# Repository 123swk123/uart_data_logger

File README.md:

# UART data logger to SD card

> [!NOTE]
> *Work in progress...*

This is a simple UART data logger, logger saves the data to FAT(12/16/32) formatted SD card.

## Schematic

## Preparations

- Any SDHC card should work, but I have tested them upto 8GB
- Format the card as FAT12/16/32
- copy the [config.txt](src/card_config/config.txt) and [head](src/card_config/head) to root of the SD card

## How to use the logger

- After power-on the status LED will be OFF
- start/stop button is a simple toggle switch
    - press once to start logging
    - press again to stop logging
- Always remove the card when status LED is OFF.

| Status LED | Remarks |
|--|--|
| OFF | Logger stopped, free to remove the SD card after powering down |
| ON | Logger running, do not remove the card |
| Constant blinking | Logger error |
| Brief pulsing |  Actively logging the received UART data |

### config.txt

first 2 lines are comment and they are skipped during the configuration process

3rd line describes the serial port configuration.
> `s<no>:baud rate,data bits<8,9>,parity<0,1,2>,stop bits<1,2>,output formatter<c,d,x,X>,seq start char,seq end char`
```
s<no>:    Serial port number, starting from 1
range:    1 to Maximum no.of UART HW supported by the controller, in case of CH32V003 its just 1.
Example:  s1
```
```
baud rate:  UART logger baud rate
range:      1200 ~ 300000 (check CH32v003 reference manual to calculate the percentage error due to divider round off)
Example:    115200
```
```
data bits:  UART logger data bits per frame
range:      8, 9
Example:    8
```
```
parity:   UART data partiy enable/disable
range:    0 - No parity (disabled)
          1 - odd parity
          2 - even parity
Example:  0
```
```
stop bits:  No.of stop bits per frame
range:      1, 2
Example:    1
```
```
output formatter: logger output encode format
range:            c - store the UART data in a transparent 8-bit ASCII raw
                  u - store the UART data as unsigned decimal value
                  x - store the UART data as hexadecimal value
                  X - store the UART data as hexadecimal value (all caps)
Example:          x
```
```
seq start char: a 9-bit unsigned integer. Upon reciving this character logger notes the event time stamp at start of the row/line
                and the logger continues to log the sub-sequent received data in the same row/line as per the output format
                Note: This seq start character will not be logged.
                      time stamp format: hour.minute.seconds.milli second (resolution: 100milli)
range:          0 ~ 511
Example:        13 (\r)
```
```
seq stop char:  a 9-bit unsigned integer. Upon reciving this character logger closes the current row/line with \r\n and
                creates a new row/line, then the logger waits for seq start character.
                Note: seq stop character will not be logged; Seq start and stop char can be the same.
range:          0 ~ 511
Example:        10 (\n)
```

4th line describes the time offset information.
> `t:year,month,day,hour,minute`
```
t:  start of time offset definition

year:     unsigned 16bit integer
range:    > 1980
Example:  2026

month:    unsigned 16bit integer
range:    1 ~ 12
Example:  2

day:      unsigned 16bit integer
range:    1 ~ 31
Example:  10

hour:     unsigned 16bit integer
range:    0 ~ 23
Example:  22

minute:   unsigned 16bit integer
range:    0 ~ 59
Example:  0
```

### Reasons for logger error

1. SD card not present
2. SD card format not recognized, so unable to mount
3. missing [config.txt](src/card_config/config.txt) in the root of SD card
4. missing [head](src/card_config/head) in the root of SD card
5. Invalid / Un-recognizable contents in [config.txt](src/card_config/config.txt) or [head](src/card_config/head)

## [How to build](docs/build.md)

## Tested features

> [!WARNING]
> Not all aspects of the functionality was tested (This was a side project)

- SDHC card upto 8GB
- Tested baud
  - 115200
  - 750000
  - 921600
- Data bits
  - 8
  - 9
- Parity
  - None
- Stop bits
  - 2
- Logging format
  - `c` - ASCII characters
  - `u` - unsigned decimal
  - `x`/`X` - Hexadecimal
- Seq start/Seq stop
  - `\r`
  - `0xFF`
  - `0x1CC`

### Sample log output
[Test log results](docs/log_output.md)

### Thanks to various open source code base helped realizing the project

- Framework [ch32fun](https://github.com/cnlohr/ch32fun)
- SD Card driver [modified sample driver from ChaN](https://elm-chan.org/docs/mmc/mmc_e.html)
- FAT(12/16/32) library [ChaN's FatFs](https://elm-chan.org/fsw/ff/)
- [Aleksej Muratov's sscanf](https://github.com/MuratovAS/mini-scanf) modified for this project to further reduce the ROM size

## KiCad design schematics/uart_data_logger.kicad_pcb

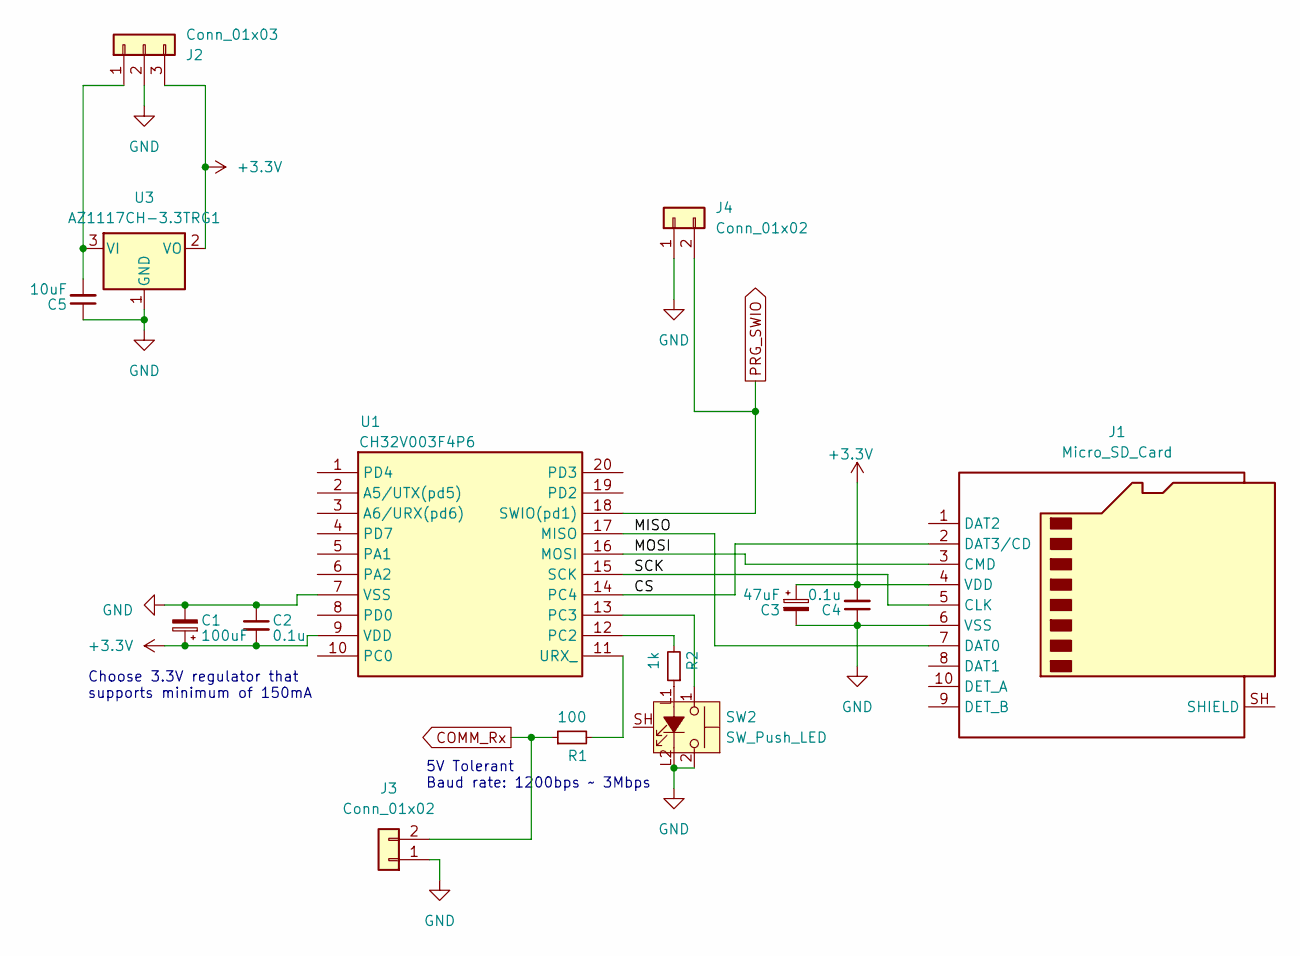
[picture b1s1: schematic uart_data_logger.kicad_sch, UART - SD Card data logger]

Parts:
C1: 100uF; C_1206_3216Metric_Pad1.33x1.80mm_HandSolder
C2, C4: 0.1u; C_1206_3216Metric_Pad1.33x1.80mm_HandSolder
C3: 47uF; C_1206_3216Metric_Pad1.33x1.80mm_HandSolder
C5: 10uF; C_1206_3216Metric_Pad1.33x1.80mm_HandSolder
J1: Micro_SD_Card; microSD_HC_Hirose_DM3AT-SF-PEJM5
J2: Conn_01x03; 1x03_THT_P2.54mm
J3, J4: Conn_01x02; 1x02_THT_P2.54mm
R1: 100; R_1206_3216Metric_Pad1.30x1.75mm_HandSolder
R2: 1k; R_1206_3216Metric_Pad1.30x1.75mm_HandSolder
SW2: SW_Push_LED; SW_Push_LED_AK104238
U1: CH32V003F4P6; TSSOP20
U3: AZ1117CH-3.3TRG1; SOT-223-3_TabPin2

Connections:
+3.3V: C1.1, C2.2, C3.1, C4.2, J1.4 (VDD), J2.3, U1.9 (VDD), U3.2 (VO)
/CS: J1.2 (DAT3/CD), U1.14 (PC4)
/MISO: J1.7 (DAT0), U1.17 (MISO)
/MOSI: J1.3 (CMD), U1.16 (MOSI)
/SCK: J1.5 (CLK), U1.15 (SCK)
COMM_Rx: J3.2, R1.1
GND: C1.2, C2.1, C3.2, C4.1, C5.1, J1.6 (VSS), J2.2, J3.1, J4.1, SW2.2, SW2.L2, U1.7 (VSS), U3.1 (GND)
unnamed: C5.2, J2.1, U3.3 (VI)
unnamed: R2.1, SW2.L1
unnamed: R1.2, U1.11 (URX_)
unnamed: R2.2, U1.12 (PC2)
unnamed: SW2.1, U1.13 (PC3)
PRG_SWIO: J4.2, U1.18 (SWIO(pd1))

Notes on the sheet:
5V Tolerant Baud rate: 1200bps ~ 3Mbps
Choose 3.3V regulator that supports minimum of 150mA

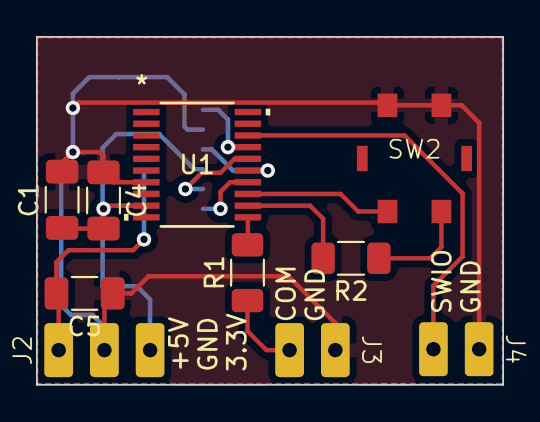
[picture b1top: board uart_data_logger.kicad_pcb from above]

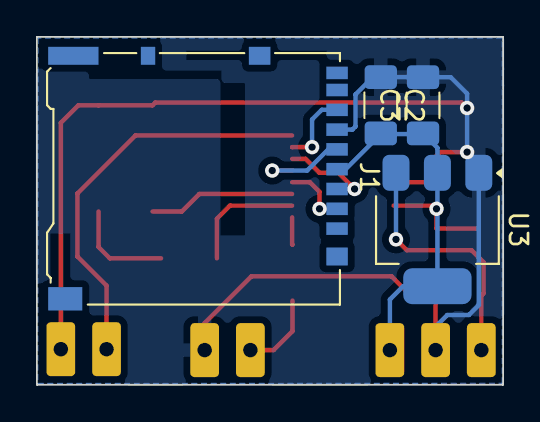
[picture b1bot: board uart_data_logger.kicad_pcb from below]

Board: 2 copper layers, 25.9 x 19.3 mm, 14 parts (4 on the bottom side), 13 nets.

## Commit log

2026-02-03 added schematic
2026-02-03 Initial work in progress version
2026-02-12 optimization for continuous stream of data.
    - write cache
    - fixed decimal/hexadecimal logging
    - build config to choose reload options.
2026-02-13 added configuration and usage details
2026-02-15 Added Tests and fixed RTC init issue.
2026-02-16 updated with build instructions
2026-02-16 build doc update
2026-02-25 fix for empty 0KB log files
2026-02-27 fixed logging failure
    1. improved SD driver writing speed
    2. timing resolution changed to 50ms
    3. LED error blink rate changed to 0.5Hz
    4. buffer handling issue.
2026-03-04 code clean-up, aligned write.
    - log streamlining
    - improved periodic sync
    - sector aligned io-write
    - fix for random disk_write failures
2026-03-23 Fixed spurious SD write failure
    1. SPI Tx/Rx DMA priority fix
    2. nested systick support
    3. improved error status reporting
2026-04-01 updated schematics/layout.

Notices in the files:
schematics/uart_data_logger.kicad_sch:
©swk
